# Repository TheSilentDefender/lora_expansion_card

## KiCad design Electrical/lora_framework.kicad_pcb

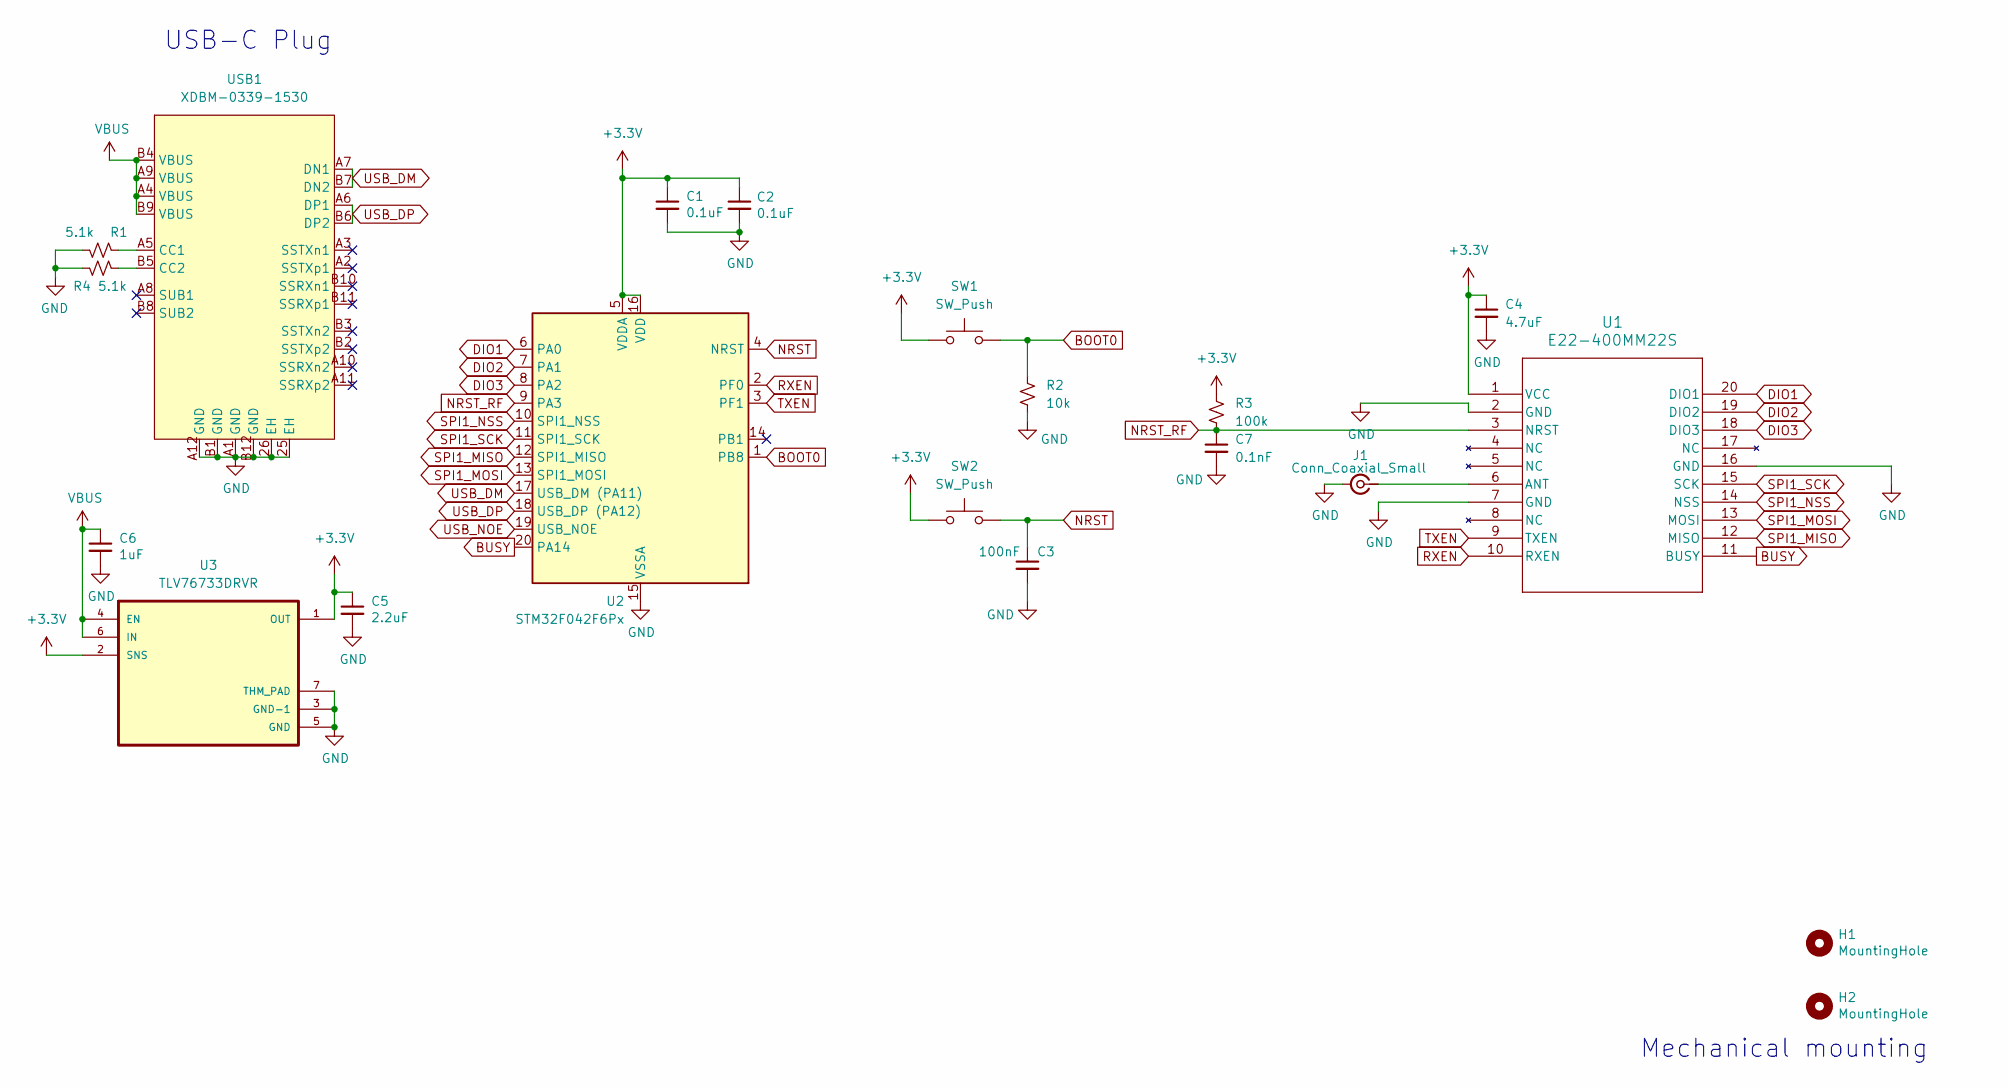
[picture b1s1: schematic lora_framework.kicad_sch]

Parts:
C1, C2: 0.1uF; C_0402_1005Metric
C3: 100nF; C_0402_1005Metric; LCSC C307331
C4: 4.7uF; C_0402_1005Metric
C5: 2.2uF; C_0402_1005Metric
C6: 1uF; C_0402_1005Metric
C7: 0.1nF; C_0402_1005Metric
H1, H2: MountingHole; MountingHole_2.2mm_M2
J1: Conn_Coaxial_Small; MMCX_Molex_73415-0961_Horizontal_1.6mm-PCB
R1, R4: 5.1k; R_0402_1005Metric
R2: 10k; R_0402_1005Metric
R3: 100k; R_0402_1005Metric
SW1, SW2: SW_Push; SW_Push_SPST_NO_Alps_SKRK
U1: E22-400MM22S; MOD20_E22-400MM22S_CGD-M
U2: STM32F042F6Px; TSSOP-20_4.4x6.5mm_P0.65mm
U3: TLV76733DRVR; SON65P200X200X80-7N
USB1: XDBM-0339-1530; USB-C-SMD_USB-3.1-C-TYPE; LCSC Part C7527710

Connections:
+3.3V: C1.1, C2.1, C4.1, C5.1, R3.1, SW1.1, SW2.1, U1.1 (VCC), U2.5 (VDDA), U2.16 (VDD), U3.1 (OUT), U3.2 (SNS)
BOOT0: R2.1, SW1.2, U2.1 (PB8)
BUSY: U1.11 (BUSY), U2.20 (PA14)
DIO1: U1.20 (DIO1), U2.6 (PA0)
DIO2: U1.19 (DIO2), U2.7 (PA1)
DIO3: U1.18 (DIO3), U2.8 (PA2)
GND: C1.2, C2.2, C3.2, C4.2, C5.2, C6.2, C7.2, J1.2 (Ext), R1.2, R2.2, R4.1, U1.2 (GND), U1.7 (GND), U1.16 (GND), U2.15 (VSSA), U3.3 (GND-1), U3.5 (GND), U3.7 (THM_PAD), USB1.25 (EH), USB1.26 (EH), USB1.A1 (GND), USB1.A12 (GND), USB1.B1 (GND), USB1.B12 (GND)
NRST: C3.1, SW2.2, U2.4 (NRST)
NRST_RF: C7.1, R3.2, U1.3 (NRST), U2.9 (PA3)
unnamed: J1.1 (In), U1.6 (ANT)
unnamed: R1.1, USB1.A5 (CC1)
unnamed: R4.2, USB1.B5 (CC2)
RXEN: U1.10 (RXEN), U2.2 (PF0)
SPI1_MISO: U1.12 (MISO), U2.12 (SPI1_MISO)
SPI1_MOSI: U1.13 (MOSI), U2.13 (SPI1_MOSI)
SPI1_NSS: U1.14 (NSS), U2.10 (SPI1_NSS)
SPI1_SCK: U1.15 (SCK), U2.11 (SPI1_SCK)
TXEN: U1.9 (TXEN), U2.3 (PF1)
USB_DM: U2.17 (USB_DM (PA11)), USB1.A7 (DN1), USB1.B7 (DN2)
USB_DP: U2.18 (USB_DP (PA12)), USB1.A6 (DP1), USB1.B6 (DP2)
USB_NOE: U2.19 (USB_NOE)
VBUS: C6.1, U3.4 (EN), U3.6 (IN), USB1.A4 (VBUS), USB1.A9 (VBUS), USB1.B4 (VBUS), USB1.B9 (VBUS)

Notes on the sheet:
USB-C Plug
Mechanical mounting

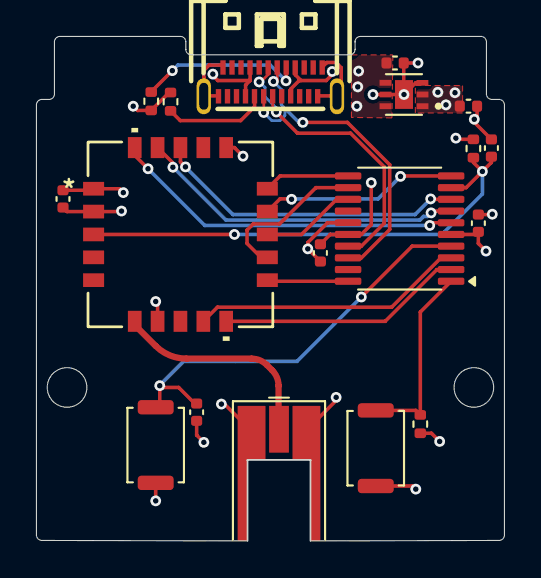
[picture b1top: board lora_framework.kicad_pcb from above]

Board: 4 copper layers, 26.0 x 28.0 mm, 20 parts (0 on the bottom side), 21 nets.

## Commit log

2025-01-03 added kicad files
2025-01-03 Create LICENSE
2026-01-01 swapped USB connector for easier assemb
